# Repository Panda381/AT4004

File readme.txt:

AT4004
Intel 4004 and 4040 4-bit processor development kit
with Busicom 141-PF calculator emulation

Last Update: 10/03/2021

open source

(c) Miroslav Nemecek
Panda38@seznam.cz

project home web page: http://www.breatharian.eu/hw/at4004/index_en.html
AT4004 on GitHub: https://github.com/Panda381/AT4004

Description

The AT4004 is a development and tutorial kit used to provide a basic introduction to programming the Intel 4004 and 4040 4-bit processor. The processor is simulated in real time using the ATmega8 processor, timed by an internal 8 MHz oscillator. The kit includes an emulation of the Busicom 141-PF calculator. Emulated programs can be compiled either as part of the built-in ROM of the ATmega8 processor, or edited by writing directly to the internal EEPROM memory in the built-in editor. From the emulated program, the 4-bit input and output ports can be accessed, brought out to both the CANON 9-pin connector and the built-in buttons and LEDs. It is also possible to access the other buttons and the character LCD display.

A ROM memory of 14 pages of 256 bytes (3584 bytes at addresses 0x000 to 0xDFF) and an EEPROM memory for direct program editing of 2 pages of 256 bytes (512 bytes at addresses 0xE00 to 0xFFF) are available for the emulated program. As RAM, the emulated program has 5 memory banks, that is a total of 1600 digits or 800 bytes. The kit can be powered via a USB cable either from the computer's USB connector or from a USB +5V charger.

The Busicom 141-PF calculator (the UniCom 141P was the OEM version) was developed in 1971 and was based on the Intel 4004 processor, which was developed by Intel for this purpose. The processor operated with a clock frequency of 740 kHz and instruction times of 10.8 and 21.6 us. The calculator did not contain a display but a printer with a rotary print drum and a print width of 18 characters. The calculator could display up to 14 floating-point digits and internally calculated to 16 digits.

Wiring diagram

The USB connector is only used to power the kit from an external +5V charger or from the USB port. The processor uses an internal 8 MHz RC oscillator. Outputs from the processor are connected to the LEDs via 2K2 resistors and to the port via 470 resistors. The values of the resistors for the LEDs may need to be adjusted to the luminosity of the LEDs used. The input pins of the port are connected in parallel to the buttons. If you connect output signals to the port, do not use buttons for the inputs to avoid shorting the connected outputs. Resistor R1 controls the bias voltage for the display contrast. You may need to change it to a different value for a different display, typically 1K is better for some displays. Resistor R2 controls the intensity of the display backlight.

Construction

The circuit board has a size of 100 x 75 mm and the free version of Eagle can be used to design it. I make the PCB using photo path from photocuprextit, here just one side is sufficient. Micro switches without additional fingerboard are used as buttons. A paper label with button labels and button holes cut out can be folded over the buttons. The processor is plugged into a DIP28 socket, this allows for easy replacement when replacing an emulated ROM version or when damaged through ports. The LCD is connected to the board via a pin and pinhole rail and can thus be easily removed. The surface joint is ready for both a 5.7 mm and 8 mm high pinhole rail.

Starting Up

When programming the firmware into the ATmega8 processor it is necessary to set the processor fuses as follows: LOW = 0xE4, HIGH = 0xD1 (the processor works with the internal 8 MHz RC generator). Be careful if you use a processor from another device switched to an external crystal - in this kit (without crystal) it may not be possible to program it, it may be necessary to connect a crystal externally to the processor. This does not apply to a new unused processor, this is always switched to the internal RC oscillator.

The display backlight should light up when power is connected. When the processor and display are working properly, the opening text should appear for less than a second. If the text is not visible, you may just need to lower the display contrast resistance R1 from 2K2 to 1K0.

How to use the kit

When you turn on the AT4004 kit, the programming edit mode will start (in the photo with the programming button label on).

In the programming mode it is possible to view the emulated program in ROM memory (address 0x000 to 0xDFF) and edit the program in EEPROM memory (address 0xE00 to 0xFFF). The first row of the display shows the 5 bytes of memory around the current address. The byte from the current address is delimited by slash brackets. The second row of the display shows the contents of the current address: the address, the contents of the address in HEX code, and the simplified mnemonic of the instruction (without parameters).

The program can be scrolled through with the SST (step forward) and BST (step backward) buttons. Scrolling is byte by byte, not instruction by instruction. The GTO button can be used to jump to a specified address. The address entry can be interrupted by pressing e.g. SST or BST. When editing a program in EEPROM (addresses 0xE00 to 0xFFF), a new byte value is written by entering 2 HEX digits. The entry can be interrupted by pressing e.g. SST or BST. The program can be started either from the current address with the 2ND RUN button or from the beginning of 256B page 0..15 with the 2ND RUN0 to RUNF buttons. The started program is interrupted by pressing RESET. The 2ND button selects an alternative button function. DEL and INS delete or insert a byte at the current address, but only within the range of the current 256B page.

Busicom 141-PF calculator emulation

To start the Busicom 141-PF calculator emulation after switching on the kit, press the 2ND RUN buttons (start from the current address 0) or press 2ND RUN0. The display of the kit emulates the output to the printer and so the data appears only after some operation has been performed.

LED indicators: M (yellow) is non-zero memory content, OVF (red) overflow, NEG (green) negative result.

The sum of '+' and the difference '-' is working with the accumulator. First enter the number and then the '+' or '-' operation to be performed on the number. Finally, the accumulator contents are displayed with '='. For example, you would enter '3 - 2 =' as '3 + 2 - ='.

When multiplying by 'x' and dividing by ':', follow the same procedure as with current calculators, e.g. "2 x 3 =".

Press the calculator buttons slowly, about 2 presses per second maximum, otherwise some presses may be lost (the keyboard operation is slow).

The setting of the number of decimal places and the rounding mode will only become apparent the next time the result is output. The 'FL' (floating) rounding mode will display the number with maximum precision with the removal of insignificant zeros, but will only appear for multiplication and division. '54' mode rounds the result, 'N' mode disables rounding. 'DP0' to 'DP8' sets the number of decimal places to 0 to 8.

'C' clears everything (except memory), 'CE' clears a wrong entry. 'S' is used to enter a negative number. 'SUB' displays the intermediate result of addition and subtraction. 'EX' swaps registers during multiplication and division. 'CM' displays memory and clears it. 'RM' displays memory and keeps it. 'M+' and 'M-' add or subtract a number from memory. 'ADV' is paper shift (line feed).

Sample Programs

The sample programs can be compiled using the included AS4 compiler. From the compilation listing, write the HEX codes into the EEPROM memory of the kit and run the program. The source codes for the sample programs can be found in the AT4004 firmware source code.

Example 1 - copy input to output

Write the program from address 0xE00 and run it with the 2ND RUNE buttons. Pressing the IN0..IN3 buttons will light the LEDs on OUT0 to OUT3.

E00 F0
E01 FD
E02 20 30
E04 21
E05 EA
E06 F4
E07 20 40
E09 21
E0A E1
E0B 4E 02

Example 2 - Flashing with LED

Write the program from address 0xE80 and run with the GTO E 8 0 2ND RUN buttons. The LEDs will flash alternately with a delay of 250 ms.

E80 F0
E81 FD
E82 20 40
E84 21
E85 D1
E86 E1
E87 5E 97
E89 D2
E8A E1
E8B 5E 97
E8D D4
E8E E1
E8F 5E 97
E91 D8
E92 E1
E93 5E 97
E95 4E 85
E97 22 D5
E99 24 6F
E9B 75 9B
E9D 74 9B
E9F 73 9B
EA1 72 9B
EA3 C0

Example 3 - text display

Write the program from address 0xF00 and run it with the 2ND RUNF buttons. The display shows the text.

F00 22 40
F02 23
F03 D0
F04 E2
F05 22 60
F07 23
F08 20 18
F0A 34
F0B A4
F0C E2
F0D A5
F0E E2
F0F 61
F10 A1
F11 1C 14
F13 60
F14 73 0A
F16 4F 16
F18 2A
F19 20
F1A 48
F1B 65
F1C 6C
F1D 6C
F1E 6F
F1F 20
F20 57
F21 6F
F22 72
F23 6C
F24 64
F25 21
F26 20
F27 2A

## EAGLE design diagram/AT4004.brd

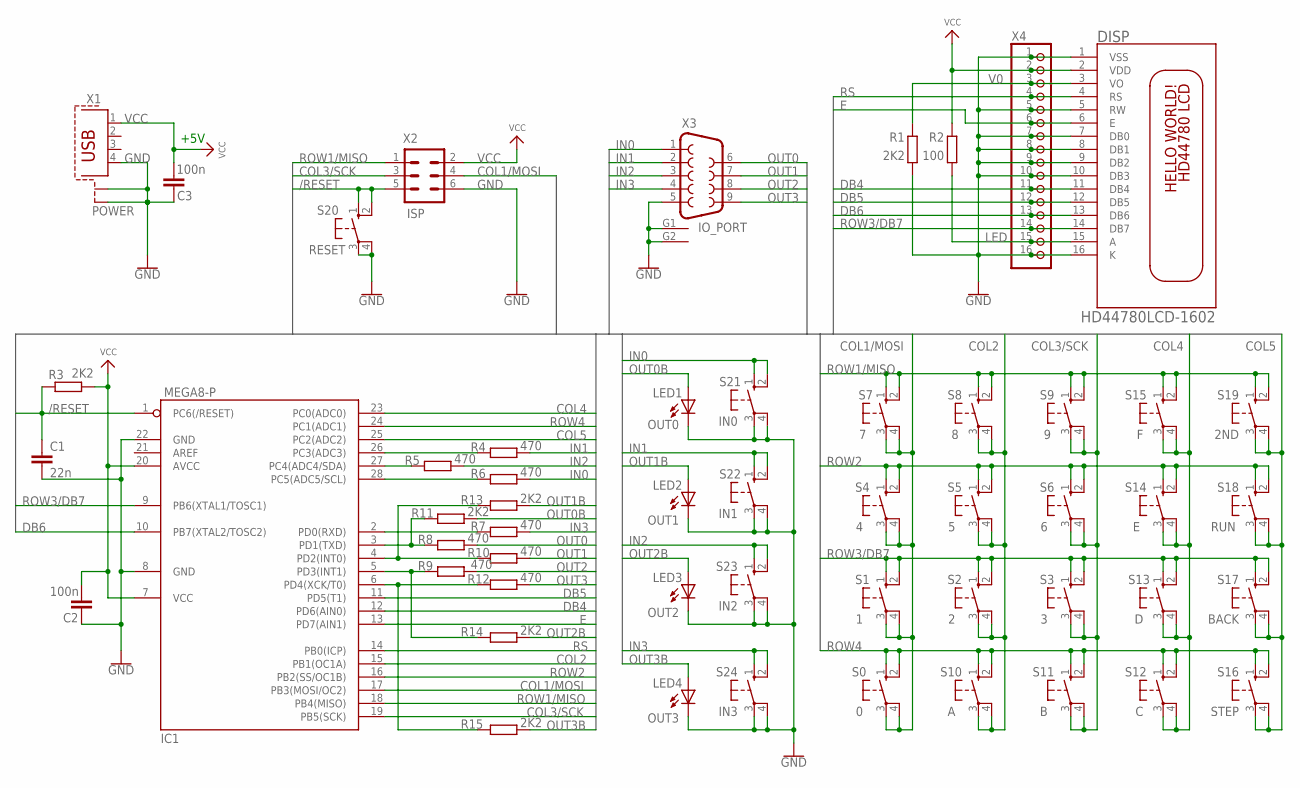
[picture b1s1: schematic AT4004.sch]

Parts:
C1: 22n; C050-024X044
C2, C3: 100n; C050-024X044
DISP: HD44780LCD-1602; LCD1602
IC1: MEGA8-P; DIL28-3
LED1: OUT0; LED3MM
LED2: OUT1; LED3MM
LED3: OUT2; LED3MM
LED4: OUT3; LED3MM
R1, R11, R13, R14, R15: 2K2; 0204/10
R2: 100; 0204/10
R3: 2K2; 0204/7
R4, R5, R7, R8, R10, R12: 470; 0204/10
R6, R9: 470; 0204/7
S0: 0; B3F-10XX
S1: 1; B3F-10XX
S2: 2; B3F-10XX
S3: 3; B3F-10XX
S4: 4; B3F-10XX
S5: 5; B3F-10XX
S6: 6; B3F-10XX
S7: 7; B3F-10XX
S8: 8; B3F-10XX
S9: 9; B3F-10XX
S10: A; B3F-10XX
S11: B; B3F-10XX
S12: C; B3F-10XX
S13: D; B3F-10XX
S14: E; B3F-10XX
S15: F; B3F-10XX
S16: STEP; B3F-10XX
S17: BACK; B3F-10XX
S18: RUN; B3F-10XX
S19: 2ND; B3F-10XX
S20: RESET; B3F-10XX
S21: IN0; B3F-10XX
S22: IN1; B3F-10XX
S23: IN2; B3F-10XX
S24: IN3; B3F-10XX
X1: POWER; PN61729-S
X2: ISP; ML6
X3: IO_PORT; DB9
X4: PINHD-1X16/90; 1X16/90

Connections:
/RESET: C1.1, IC1.1 (PC6(/RESET)), R3.2, S20.1 (S), S20.2 (S1), X2.5
COL1/MOSI: IC1.17 (PB3(MOSI/OC2)), S0.3, S0.4 (P1), S1.3, S1.4 (P1), S4.3, S4.4 (P1), S7.3, S7.4 (P1), X2.4
COL2: IC1.15 (PB1(OC1A)), S2.3, S2.4 (P1), S5.3, S5.4 (P1), S8.3, S8.4 (P1), S10.3, S10.4 (P1)
COL3/SCK: IC1.19 (PB5(SCK)), S3.3, S3.4 (P1), S6.3, S6.4 (P1), S9.3, S9.4 (P1), S11.3, S11.4 (P1), X2.3
COL4: IC1.23 (PC0(ADC0)), S12.3, S12.4 (P1), S13.3, S13.4 (P1), S14.3, S14.4 (P1), S15.3, S15.4 (P1)
COL5: IC1.25 (PC2(ADC2)), S16.3, S16.4 (P1), S17.3, S17.4 (P1), S18.3, S18.4 (P1), S19.3, S19.4 (P1)
DB4: DISP.11 (DB4), IC1.12 (PD6(AIN0)), X4.11
DB5: DISP.12 (DB5), IC1.11 (PD5(T1)), X4.12
DB6: DISP.13 (DB6), IC1.10 (PB7(XTAL2/TOSC2)), X4.13
E: DISP.6 (E), IC1.13 (PD7(AIN1)), X4.6
GND: C1.2, C2.2, C3.1, DISP.1 (VSS), DISP.5 (RW), DISP.7 (DB0), DISP.8 (DB1), DISP.9 (DB2), DISP.10 (DB3), DISP.16 (K), IC1.8 (GND), IC1.22 (GND), LED1.K (C), LED2.K (C), LED3.K (C), LED4.K (C), R1.2, S20.3, S20.4 (P1), S21.3, S21.4 (P1), S22.3, S22.4 (P1), S23.3, S23.4 (P1), S24.3, S24.4 (P1), X1.4, X1.S1, X1.S2, X2.6, X3.5, X3.G1 (10), X3.G2 (11), X4.1, X4.5, X4.7, X4.8, X4.9, X4.10, X4.16
IN0: R6.1, S21.1 (S), S21.2 (S1), X3.1
IN1: R4.1, S22.1 (S), S22.2 (S1), X3.2
IN2: R5.1, S23.1 (S), S23.2 (S1), X3.3
IN3: R7.1, S24.1 (S), S24.2 (S1), X3.4
LED: DISP.15 (A), R2.2, X4.15
unnamed: IC1.26 (PC3(ADC3)), R4.2
unnamed: IC1.27 (PC4(ADC4/SDA)), R5.2
unnamed: IC1.28 (PC5(ADC5/SCL)), R6.2
unnamed: IC1.2 (PD0(RXD)), R7.2
unnamed: IC1.3 (PD1(TXD)), R8.2, R11.2
unnamed: IC1.4 (PD2(INT0)), R10.2, R13.2
unnamed: IC1.5 (PD3(INT1)), R9.2, R14.2
unnamed: IC1.6 (PD4(XCK/T0)), R12.2, R15.2
OUT0: R8.1, X3.6
OUT0B: LED1.A, R11.1
OUT1: R10.1, X3.7
OUT1B: LED2.A, R13.1
OUT2: R9.1, X3.8
OUT2B: LED3.A, R14.1
OUT3: R12.1, X3.9
OUT3B: LED4.A, R15.1
ROW1/MISO: IC1.18 (PB4(MISO)), S7.1 (S), S7.2 (S1), S8.1 (S), S8.2 (S1), S9.1 (S), S9.2 (S1), S15.1 (S), S15.2 (S1), S19.1 (S), S19.2 (S1), X2.1
ROW2: IC1.16 (PB2(SS/OC1B)), S4.1 (S), S4.2 (S1), S5.1 (S), S5.2 (S1), S6.1 (S), S6.2 (S1), S14.1 (S), S14.2 (S1), S18.1 (S), S18.2 (S1)
ROW3/DB7: DISP.14 (DB7), IC1.9 (PB6(XTAL1/TOSC1)), S1.1 (S), S1.2 (S1), S2.1 (S), S2.2 (S1), S3.1 (S), S3.2 (S1), S13.1 (S), S13.2 (S1), S17.1 (S), S17.2 (S1), X4.14
ROW4: IC1.24 (PC1(ADC1)), S0.1 (S), S0.2 (S1), S10.1 (S), S10.2 (S1), S11.1 (S), S11.2 (S1), S12.1 (S), S12.2 (S1), S16.1 (S), S16.2 (S1)
RS: DISP.4 (RS), IC1.14 (PB0(ICP)), X4.4
V0: DISP.3 (VO), R1.1, X4.3
VCC: C2.1, C3.2, DISP.2 (VDD), IC1.7 (VCC), IC1.20 (AVCC), R2.1, R3.1, X1.1, X2.2, X4.2

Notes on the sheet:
+5V

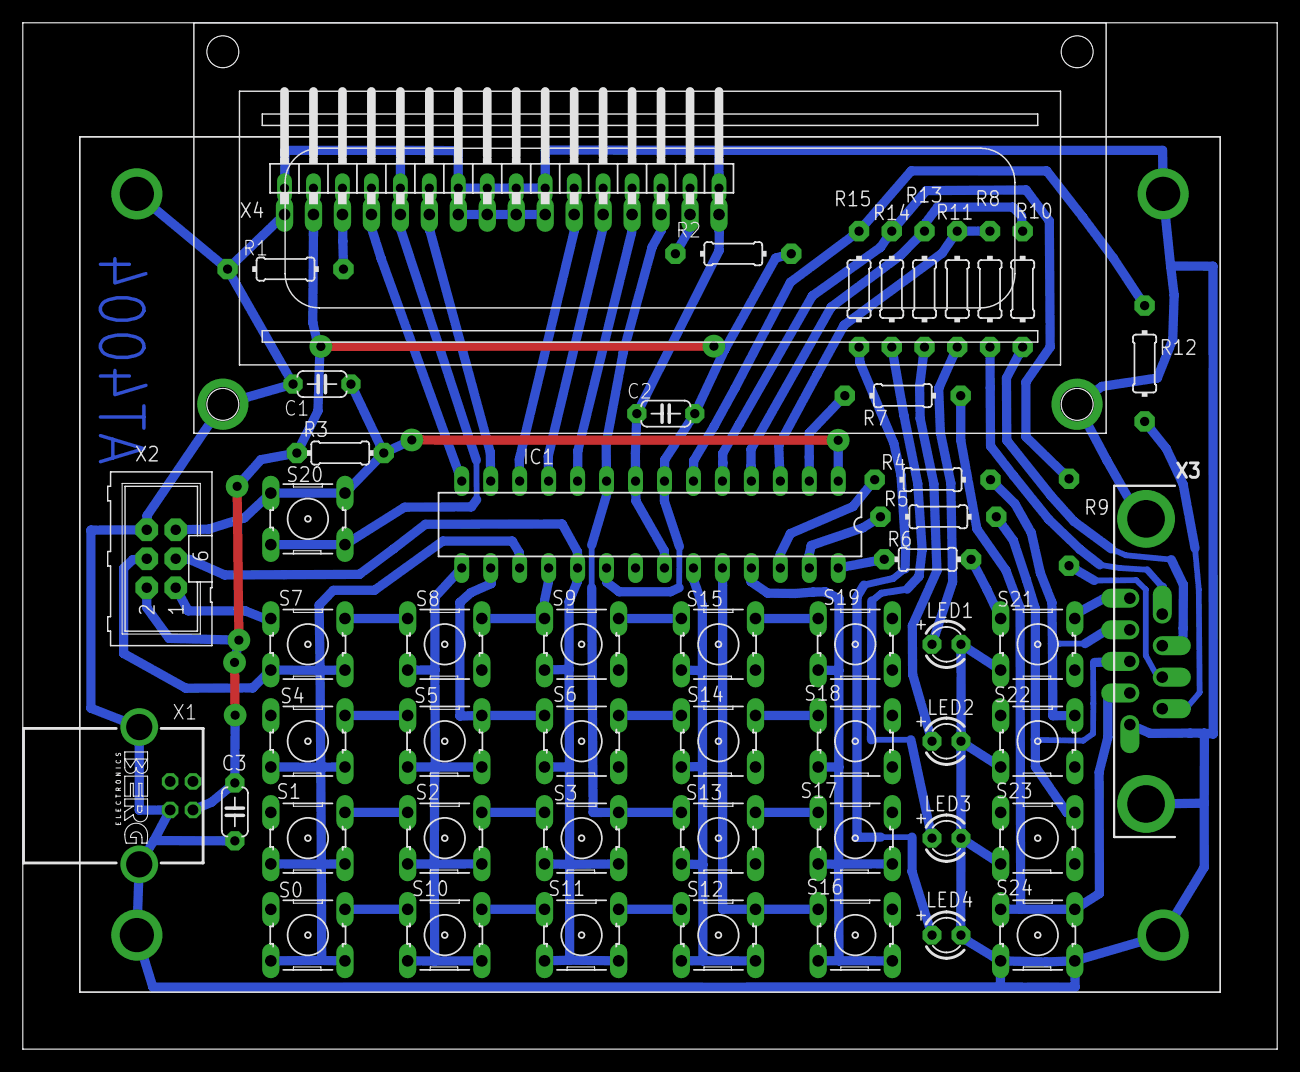
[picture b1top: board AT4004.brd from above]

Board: 2 copper layers, 110.0 x 90.0 mm, 53 parts (1 on the bottom side), 39 nets.

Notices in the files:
parts and their libraries:
SparkFun-Connectors: Licensing: Creative Commons ShareAlike 4.0 International - https://creativecommons.org/licenses/by-sa/4.0
